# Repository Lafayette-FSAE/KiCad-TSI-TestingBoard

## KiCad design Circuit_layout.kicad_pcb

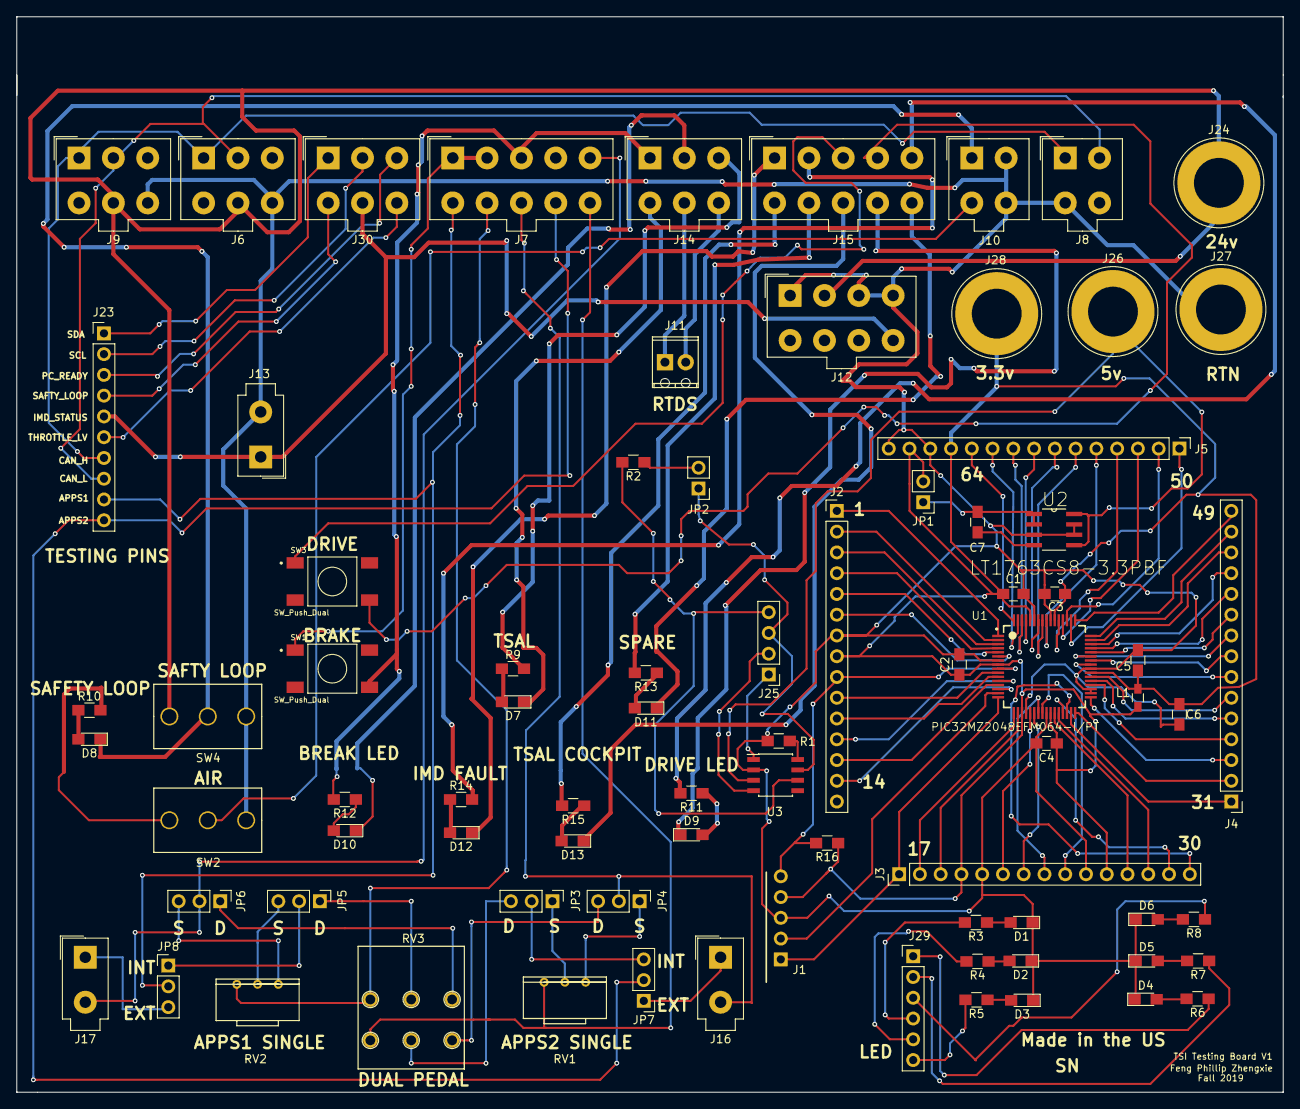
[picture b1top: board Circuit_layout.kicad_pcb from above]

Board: 2 copper layers, 154.9 x 131.6 mm, 80 parts (1 on the bottom side), 127 nets.

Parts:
C1, C2, C3, C4, C5, C6: 0.1u; C_0805_HandSoldering
C7: 1uF; C_0805_HandSoldering
D1: LED_4; LED_0805_HandSoldering
D2: LED_5; LED_0805_HandSoldering
D3: LED_6; LED_0805_HandSoldering
D4: LED_3; LED_0805_HandSoldering
D5: LED_2; LED_0805_HandSoldering
D6: LED_1; LED_0805_HandSoldering
D7: TSAL; LED_0805_HandSoldering
D8: Safety_Loop_LED; LED_0805_HandSoldering
D9: Drive_LED; LED_0805_HandSoldering
D10: Brake_LED; LED_0805_HandSoldering
D11: Spare_LED; LED_0805_HandSoldering
D12: IMD_Fault_LED; LED_0805_HandSoldering
D13: TSAL_Cock_LED; LED_0805_HandSoldering
J1: ICSP; Pin_Header_Straight_1x05_Pitch2.54mm
J2: Chip_conn1; Pin_Header_Straight_1x15_Pitch2.54mm
J3: Chip_conn2; Pin_Header_Straight_1x15_Pitch2.54mm
J4: Chip_conn3; Pin_Header_Straight_1x15_Pitch2.54mm
J5: Chip_conn4; Pin_Header_Straight_1x15_Pitch2.54mm
J6: Conn_BoardJ36; Molex_MiniFit-JR-5556-06A_2x03x4.20mm_Straight
J7: Conn_BoardJ3; Molex_MiniFit-JR-5556-10A_2x05x4.20mm_Straight
J8: Conn_BoardJ34; Molex_MiniFit-JR-5556-04A_2x02x4.20mm_Straight
J9: Conn_BoardJ35; Molex_MiniFit-JR-5556-06A_2x03x4.20mm_Straight
J10: Conn_BoardJ6; Molex_MiniFit-JR-5556-04A_2x02x4.20mm_Straight
J11: RTDS; TerminalBlock_Phoenix_MPT-2.54mm_2pol
J12: Conn_BoardJ7; Molex_MiniFit-JR-5556-08A_2x04x4.20mm_Straight
J13: Conn_BoardJ8; Molex_MiniFit-JR-5556-02A_2x01x4.20mm_Straight
J14: Conn_BoardJ21; Molex_MiniFit-JR-5556-06A_2x03x4.20mm_Straight
J15: Conn_BoardJ24; Molex_MiniFit-JR-5556-10A_2x05x4.20mm_Straight
J16: APPS2_External; Molex_MiniFit-JR-5556-02A_2x01x4.20mm_Straight
J17: APPS1_External; Molex_MiniFit-JR-5556-02A_2x01x4.20mm_Straight
J23: Testing_pins; Pin_Header_Straight_1x10_Pitch2.54mm
J24: 24v_Banana; Banana_Jack_1Pin
J25: Testing_CAN_Connector; Pin_Header_Straight_1x04_Pitch2.54mm
J26: 5v_Banana; Banana_Jack_1Pin
J27: RTN_Banana; Banana_Jack_1Pin
J28: 3.3v_Banana; Banana_Jack_1Pin
J29: Testing_connector; Pin_Header_Straight_1x06_Pitch2.54mm
J30: Testing_connector; Molex_MiniFit-JR-5556-06A_2x03x4.20mm_Straight
JP1, JP2: Jumper; Pin_Header_Straight_1x02_Pitch2.54mm
JP3, JP4, JP5, JP6, JP7, JP8: Jumper_NC_Dual; Pin_Header_Straight_1x03_Pitch2.54mm
L1: 28nH; L_0603_HandSoldering
R1: 1k; R_0805_HandSoldering
R2: 120; R_0805_HandSoldering
R3, R4, R5, R6, R7, R8: 330; R_0805_HandSoldering
R9, R10, R11, R12, R13, R14, R15, R16: 1.5k; R_0805_HandSoldering
RV1: APPS2_offset_10k; 3310C-5K-POT
RV2: APPS1_offset_10k; 3310C-5K-POT
RV3: APPS_5k; PDB182-k
SW1, SW3: SW_Push_Dual; FSM4JSMATR
SW2: Safty_loop; Switch_toggle_M2012SS1W03
SW4: Safty_loop_1; Switch_toggle_M2012SS1W03
U1: PIC32MZ2048EFM064-I/PT; QFP50P1200X1200X120-64N
U2: LT1763CS8-3.3PBF; SOIC127P600X175-8N
U3: MCP2551-I/SN; SOIC-8_3.9x4.9mm_Pitch1.27mm

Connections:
/3.3v: C1.1, C2.1, C3.1, C4.1, C5.1, C6.1, J1.4, J2.8, J3.4, J3.11, J5.12, J5.14, J28.1, JP1.2, L1.1, L1.2, R16.1, U1.8, U1.19, U1.26, U1.39, U1.54, U1.60
/5v: J26.1, U2.5, U2.8, U3.3
/24v: J6.5, J9.5, J12.2, J24.1, SW4.3
/AIRs+: J10.3, SW2.2
/AIRs-: C1.2, C2.2, C3.2, C4.2, C5.2, C6.2, D1.1, D2.1, D3.1, D4.1, D5.1, D6.1, J1.3, J2.7, J3.5, J3.10, J5.13, J5.15, J6.6, J8.3, J9.6, J10.2, J10.4, J12.1, J12.3, J12.4, J13.2, J27.1, R1.2, SW2.1, SW4.1, U1.7, U1.20, U1.25, U1.34, U1.35, U1.40, U1.55, U1.59, U2.3, U2.6, U2.7, U3.2
/APPS1: J7.6, J23.9, JP8.2
/APPS1_10: J7.5, J17.2, JP6.2
/APPS1_RTN: J7.7, RV2.1, RV3.4
/APPS2: J7.9, J23.10, JP7.2
/APPS2_5: J7.8, J16.2, JP4.2
/APPS2_RTN: J7.10, RV1.1, RV3.1
/BP: J7.3, J14.1, R12.2, SW1.4
/BP_RTN: D10.1, J14.2
/Brake_24: J7.1, J7.2, SW1.1
/CAN_H: J6.1, J8.1, J9.1, J23.7
/CAN_H_TEST: J25.3, JP2.1, U3.7
/CAN_L: J6.2, J8.2, J9.2, J23.8
/CAN_L_TEST: J25.4, R2.2, U3.6
/CAN_RX_TEST: J25.2, U3.4
/CAN_TX_TEST: J25.1, U3.1
/Drive_BTN: J15.4, SW3.4
/Drive_BTN_RTN: J15.3, SW3.1
/Drive_LED: J15.5, R11.2
/Drive_LED_RTN: D9.1, J15.9
/IMD_Fault_LED: J15.2, R14.2
/IMD_Fault_RTN: D12.1, J15.1
/IMD_Status: J12.8, J13.1, J23.5, J30.5
/LED_1: J29.1, R6.1
/LED_2: J29.2, R7.1
/LED_3: J29.3, R8.1
/LED_4: J29.4, R3.2
/LED_5: J29.5, R4.2
/LED_6: J29.6, R5.2
/PC_ready: J23.3, J30.3
/PGEC: J1.2, U1.15
/PGED: J1.1, J3.1, U1.16
/PIN1: J2.1, U1.1
/PIN2: J2.2, U1.2
/PIN3: J2.3, U1.3
/PIN4: J2.4, U1.4
/PIN5: J2.5, U1.5
/PIN6: J2.6, U1.6
/PIN10: J2.10, U1.10
/PIN11: J2.11, U1.11
/PIN12: J2.12, U1.12
/PIN13: J2.13, U1.13
/PIN14: J2.14, U1.14
/PIN17: J3.2, U1.17
/PIN18: J3.3, U1.18
/PIN21: J3.6, U1.21
/PIN22: J3.7, U1.22
/PIN23: J3.8, U1.23
/PIN24: J3.9, U1.24
/PIN27: J3.12, U1.27
/PIN28: J3.13, U1.28
/PIN29: J3.14, U1.29
/PIN30: J3.15, U1.30
/PIN31: J4.1, U1.31
/PIN32: J4.2, U1.32
/PIN33: J4.3, U1.33
/PIN36: J4.4, U1.36
/PIN37: J4.5, U1.37
/PIN38: J4.6, U1.38
/PIN41: J4.7, U1.41
/PIN42: J4.8, U1.42
/PIN43: J4.9, U1.43
/PIN44: J4.10, U1.44
/PIN45: J4.11, U1.45
/PIN46: J4.12, U1.46
/PIN47: J4.13, U1.47
/PIN48: J4.14, U1.48
/PIN49: J4.15, U1.49
/PIN50: J5.1, U1.50
/PIN51: J5.2, U1.51
/PIN52: J5.3, U1.52
/PIN53: J5.4, U1.53
/PIN56: J5.5, U1.56
/PIN57: J5.6, U1.57
/PIN58: J5.7, U1.58
/PIN61: J5.8, U1.61
/PIN62: J5.9, U1.62
/PIN63: J5.10, U1.63
/PIN64: J5.11, U1.64
/RTDS: J11.1, J14.5
/RTDS_RTN: J11.2, J14.6
/SCL: J23.2, J30.2
/SDA: J23.1, J30.1
/SL1: D8.1, J10.1, SW4.2
/SPARE_LED: J15.7, R13.2
/SPARE_LED_RTN: D11.1, J15.10
/Safety_Loop: J23.4, J30.4
/TSAL_1: J14.3, R9.2
/TSAL_1_RTN: D7.1, J14.4
/TSAL_Cock: J15.6, R15.2
/TSAL_Cock_RTN: D13.1, J15.8
/Throttle_LV: J23.6, J30.6
/~MCLR: J1.5, J2.9, R16.2, U1.9
unnamed: C7.1, JP1.1, U2.1, U2.2
unnamed: C7.2, U2.4
unnamed: D1.2, R3.1
unnamed: D2.2, R4.1
unnamed: D3.2, R5.1
unnamed: D4.2, R6.2
unnamed: D5.2, R7.2
unnamed: D6.2, R8.2
unnamed: D7.2, R9.1
unnamed: D8.2, R10.1
unnamed: D9.2, R11.1
unnamed: D10.2, R12.1
unnamed: D11.2, R13.1
unnamed: D12.2, R14.1
unnamed: D13.2, R15.1
unnamed: J16.1, JP7.1
unnamed: J17.1, JP8.3
unnamed: JP2.2, R2.1
unnamed: JP3.1, RV1.2
unnamed: JP3.2, JP7.3
unnamed: JP3.3, RV3.2
unnamed: JP4.1, RV1.3
unnamed: JP4.3, RV3.3
unnamed: JP5.1, RV3.5
unnamed: JP5.2, JP8.1
unnamed: JP5.3, RV2.2
unnamed: JP6.1, RV3.6
unnamed: JP6.3, RV2.3
unnamed: R1.1, U3.8
unnamed: R10.2, SW2.3

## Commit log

2019-09-18 back up from 2018
2019-10-17 addition conn for external pedal
